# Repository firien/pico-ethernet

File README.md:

https://github.com/firien/pico-contact-sensor

## Bill of Materials

|Tag|Qty|Value|Part|
|---|---|---|---|
|C1|1|22µF|https://www.digikey.com/en/products/detail/panasonic-electronic-components/EEE-FN1A220R/11656953|
|C2|1|10µF|https://www.digikey.com/en/products/detail/panasonic-electronic-components/EEE-HD1H100P/1985154|
|C5-6|2|30pF|https://www.digikey.com/en/products/detail/murata-electronics/GRM0335C1H300GA01D/4358722|
|C9|1|10µF|https://www.digikey.com/en/products/detail/samsung-electro-mechanics/CL10A106MQ8NNNC/3886777|
|C10,C7,C12,C4,C3,C11,C8|7|0.1µF|https://www.digikey.com/en/products/detail/murata-electronics/GRM033R60J104KE19D/702433|
|D1|1||https://www.digikey.com/en/products/detail/panjit-international-inc/MBR1020VL-R1-00001/14660471|
|FB1|1||https://www.digikey.com/en/products/detail/tai-tech-advanced-electronics-co-ltd/HFZ-1608PF-151T25/17835577|
|J1|1||https://www.digikey.com/en/products/detail/sullins-connector-solutions/PPTC201LFBN-RC/810158|
|J2|1||https://www.digikey.com/en/products/detail/sullins-connector-solutions/PPTC051LFBN-RC/807239|
|J3|1||https://www.digikey.com/en/products/detail/xp-power/VR05S05/13147728|
|J4|1||https://www.digikey.com/en/products/detail/bel-fuse-inc/SI-52003-F/1635087|
|J5|1||https://www.digikey.com/en/products/detail/phoenix-contact/1725672/267464|
|R1|1|2.32kΩ|https://www.digikey.com/en/products/detail/panasonic-electronic-components/ERJ-3EKF2321V/196189|
|R2-5|4|49.9Ω|https://www.digikey.com/en/products/detail/panasonic-electronic-components/ERJ-3EKF49R9V/196378|
|R6-7|2|180Ω|https://www.digikey.com/en/products/detail/panasonic-electronic-components/ERJ-3EKF1800V/1746322|
|U1|1||https://www.digikey.com/en/products/detail/microchip-technology/ENC28J60-I-SS/2296975|
|Y1|1|25MHz|https://www.digikey.com/en/products/detail/cts-frequency-controls/445I23E25M00000/3135168|

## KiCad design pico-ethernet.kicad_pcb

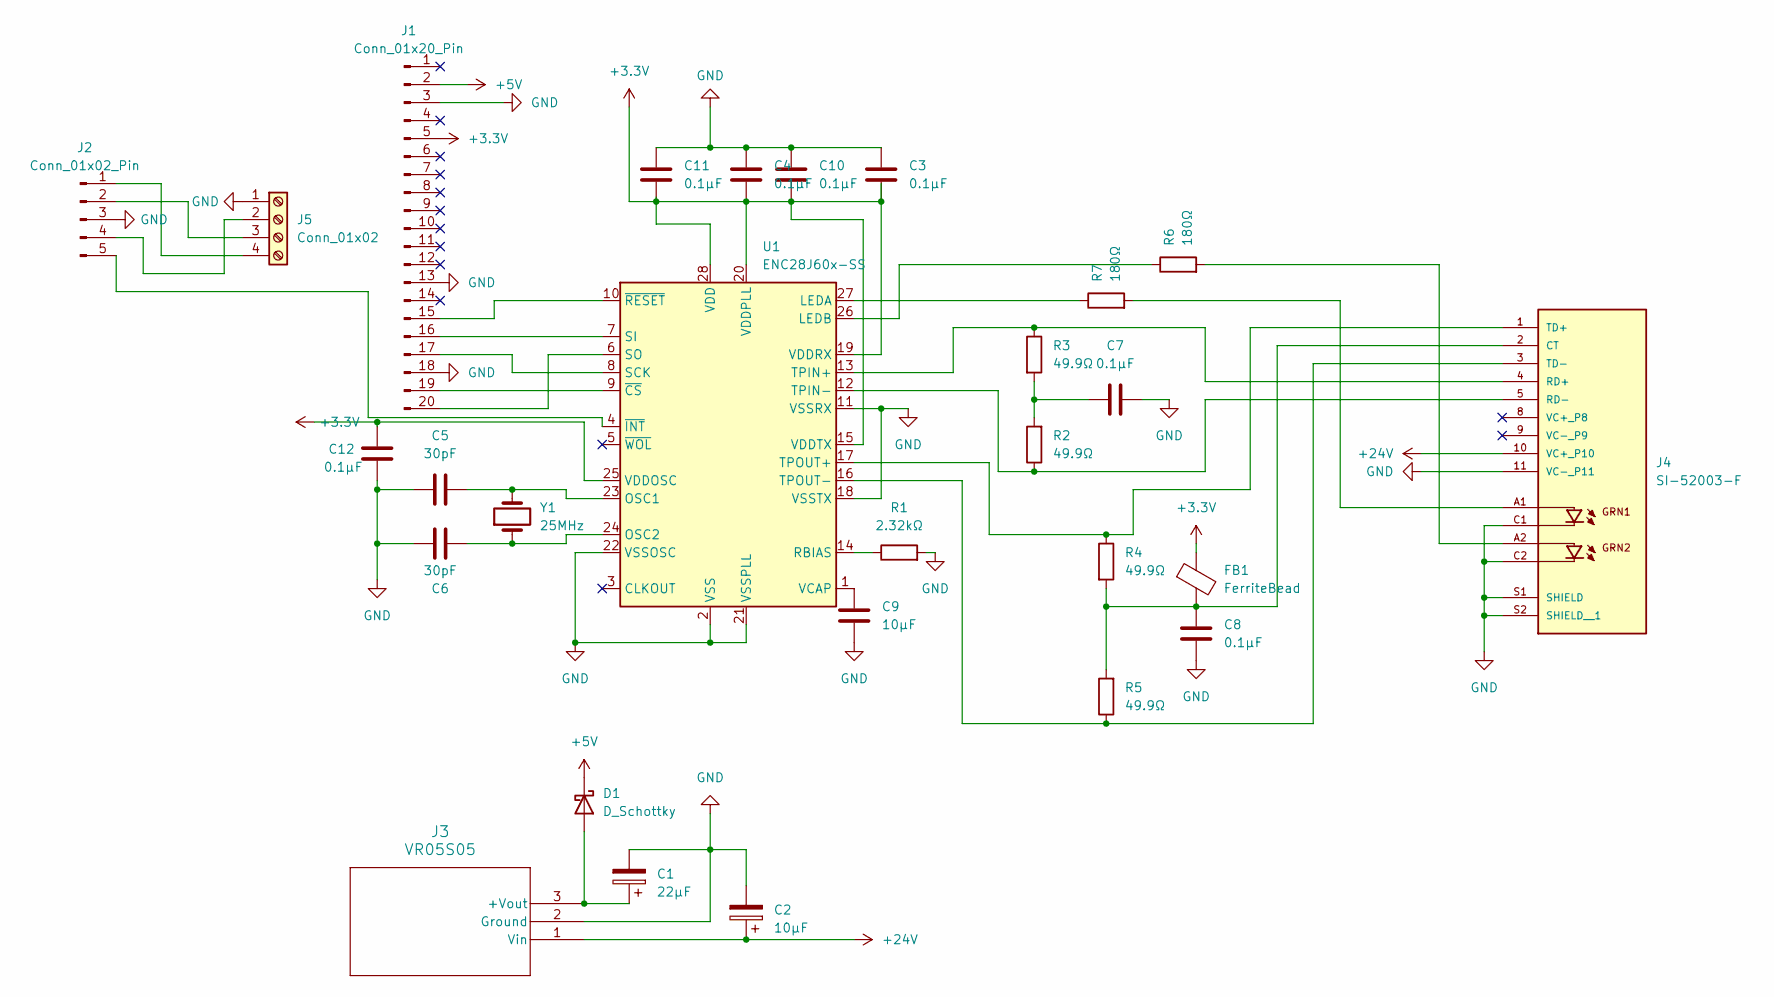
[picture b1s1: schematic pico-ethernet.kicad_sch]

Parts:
C1: 22µF; CAP_EEEFN1A220R
C2: 10µF; CAP_EEEHD1H100P
C3, C4, C7, C8, C10, C11, C12: 0.1µF; C_0603_1608Metric
C5, C6: 30pF; C_0603_1608Metric
C9: 10µF; C_0603_1608Metric
D1: D_Schottky; D_SOD-123
FB1: FerriteBead; C_0603_1608Metric
J1: Conn_01x20_Pin; PinSocket_1x20_P2.54mm_Vertical
J2: Conn_01x02_Pin; PinSocket_1x05_P2.54mm_Vertical
J3: VR05S05; CONN3_05S05_XPR
J4: SI-52003-F; BEL_SI-52003-F
J5: Conn_01x02; TerminalBlock_Phoenix_MPT-0,5-4-2.54_1x04_P2.54mm_Horizontal
R1: 2.32kΩ; R_0603_1608Metric
R2, R3, R4, R5: 49.9Ω; R_0603_1608Metric
R6, R7: 180Ω; R_0603_1608Metric
U1: ENC28J60x-SS; SSOP-28_5.3x10.2mm_P0.65mm
Y1: 25MHz; Crystal_SMD_5032-2Pin_5.0x3.2mm

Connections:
+3.3V: C3.1, C4.1, C10.1, C11.1, C12.2, FB1.1, J1.5, U1.15 (VDDTX), U1.19 (VDDRX), U1.20 (VDDPLL), U1.25 (VDDOSC), U1.28 (VDD)
+5V: D1.1 (K), J1.2
+24V: C2.1, J3.1 (Vin), J4.10 (VC+_P10)
GND: C1.2, C2.2, C3.2, C4.2, C5.1, C6.1, C7.2, C8.2, C9.2, C10.2, C11.2, C12.1, J1.3, J1.13, J1.18, J2.3, J3.2 (Ground), J4.11 (VC-_P11), J4.C1, J4.C2, J4.S1 (SHIELD), J4.S2 (SHIELD__1), J5.1, R1.2, U1.2 (VSS), U1.11 (VSSRX), U1.18 (VSSTX), U1.21 (VSSPLL), U1.22 (VSSOSC)
unnamed: C7.1, R2.2, R3.2
unnamed: C1.1, D1.2 (A), J3.3 (+Vout)
unnamed: J1.15, U1.10 (~RESET)
unnamed: J1.16, U1.7 (SI)
unnamed: J1.17, U1.8 (SCK)
unnamed: J1.19, U1.9 (~CS)
unnamed: J1.20, U1.6 (SO)
unnamed: J2.1, J5.4
unnamed: J2.2, J5.3
unnamed: J2.4, J5.2
unnamed: J2.5, U1.4 (~INT)
unnamed: C8.1, FB1.2, J4.2 (CT), R4.2, R5.2
unnamed: J4.A1, R7.2
unnamed: J4.A2, R6.2
unnamed: J4.4 (RD+), R3.1, U1.13 (TPIN+)
unnamed: J4.5 (RD-), R2.1, U1.12 (TPIN-)
unnamed: J4.1 (TD+), R4.1, U1.17 (TPOUT+)
unnamed: J4.3 (TD-), R5.1, U1.16 (TPOUT-)
unnamed: R7.1, U1.27 (LEDA)
unnamed: R6.1, U1.26 (LEDB)
unnamed: C5.2, U1.23 (OSC1), Y1.2
unnamed: C6.2, U1.24 (OSC2), Y1.1
unnamed: R1.1, U1.14 (RBIAS)
unnamed: C9.1, U1.1 (VCAP)

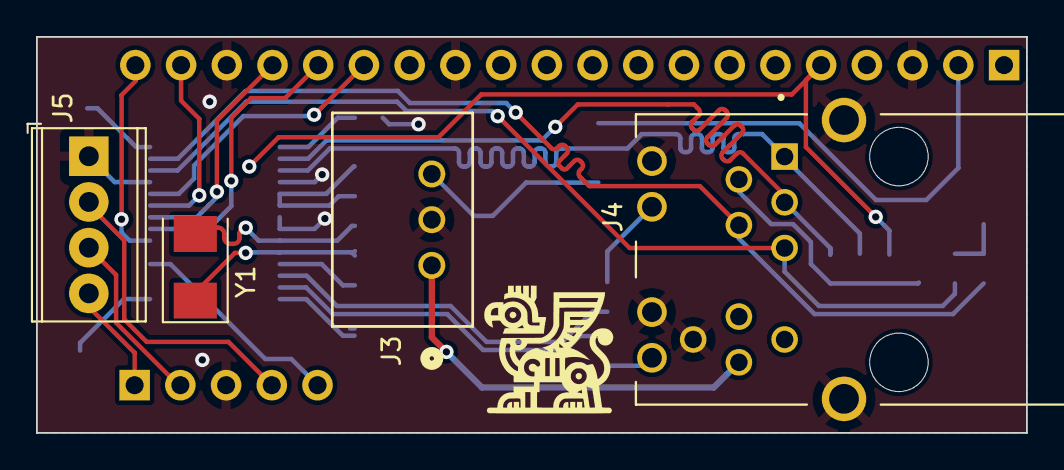
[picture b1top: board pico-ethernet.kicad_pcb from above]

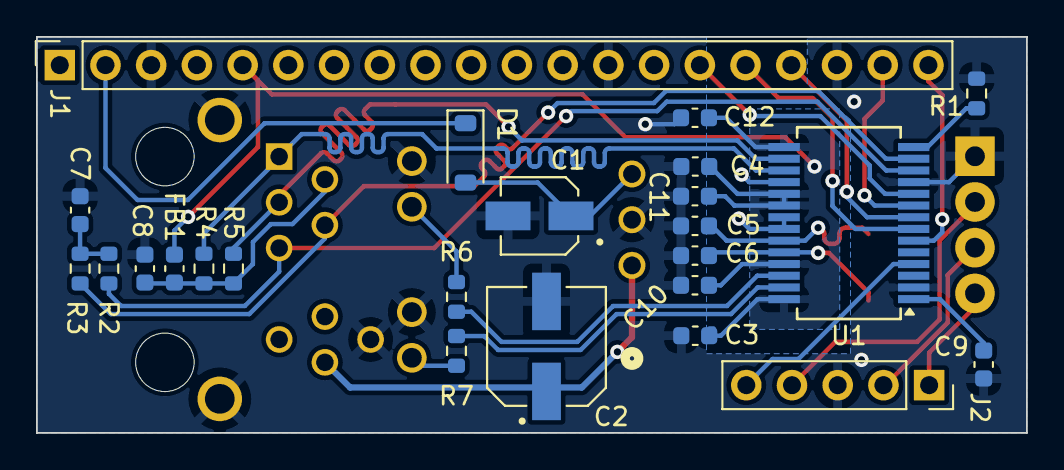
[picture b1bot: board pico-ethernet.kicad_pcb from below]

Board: 2 copper layers, 55.0 x 22.0 mm, 28 parts (24 on the bottom side), 28 nets.

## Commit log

2024-03-09 interrupt
2024-03-09 TX RX swap
2024-03-09 all good, but looks bad
2024-03-09 3v reroute
2024-03-09 3v zone
2024-03-10 tweak J2 position
2024-03-10 vanity
2024-03-10 bom update
2024-03-11 unnecessary tuning
2024-03-12 tweaks
2024-03-12 connect reset
2024-03-12 move oscillator away from vias
2024-03-22 fix quantity
